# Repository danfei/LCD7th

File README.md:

LCD7th
============
It is an Arduino compatible board.
 
Schematic
------------
[PDF][schem]

BOM
------------
[CSV][bom]

PCB
------------

Photo
------------

License
------------
This project is released under the CC BY-SA license.

Support
------------
dan@szdiy.org

Where to buy
------------

[schem]:https://github.com/danfei/LCD7th/blob/master/hardware/LCD7th.pdf
[bom]:https://github.com/danfei/LCD7th/blob/master/hardware/manufature/LCD7th.csv

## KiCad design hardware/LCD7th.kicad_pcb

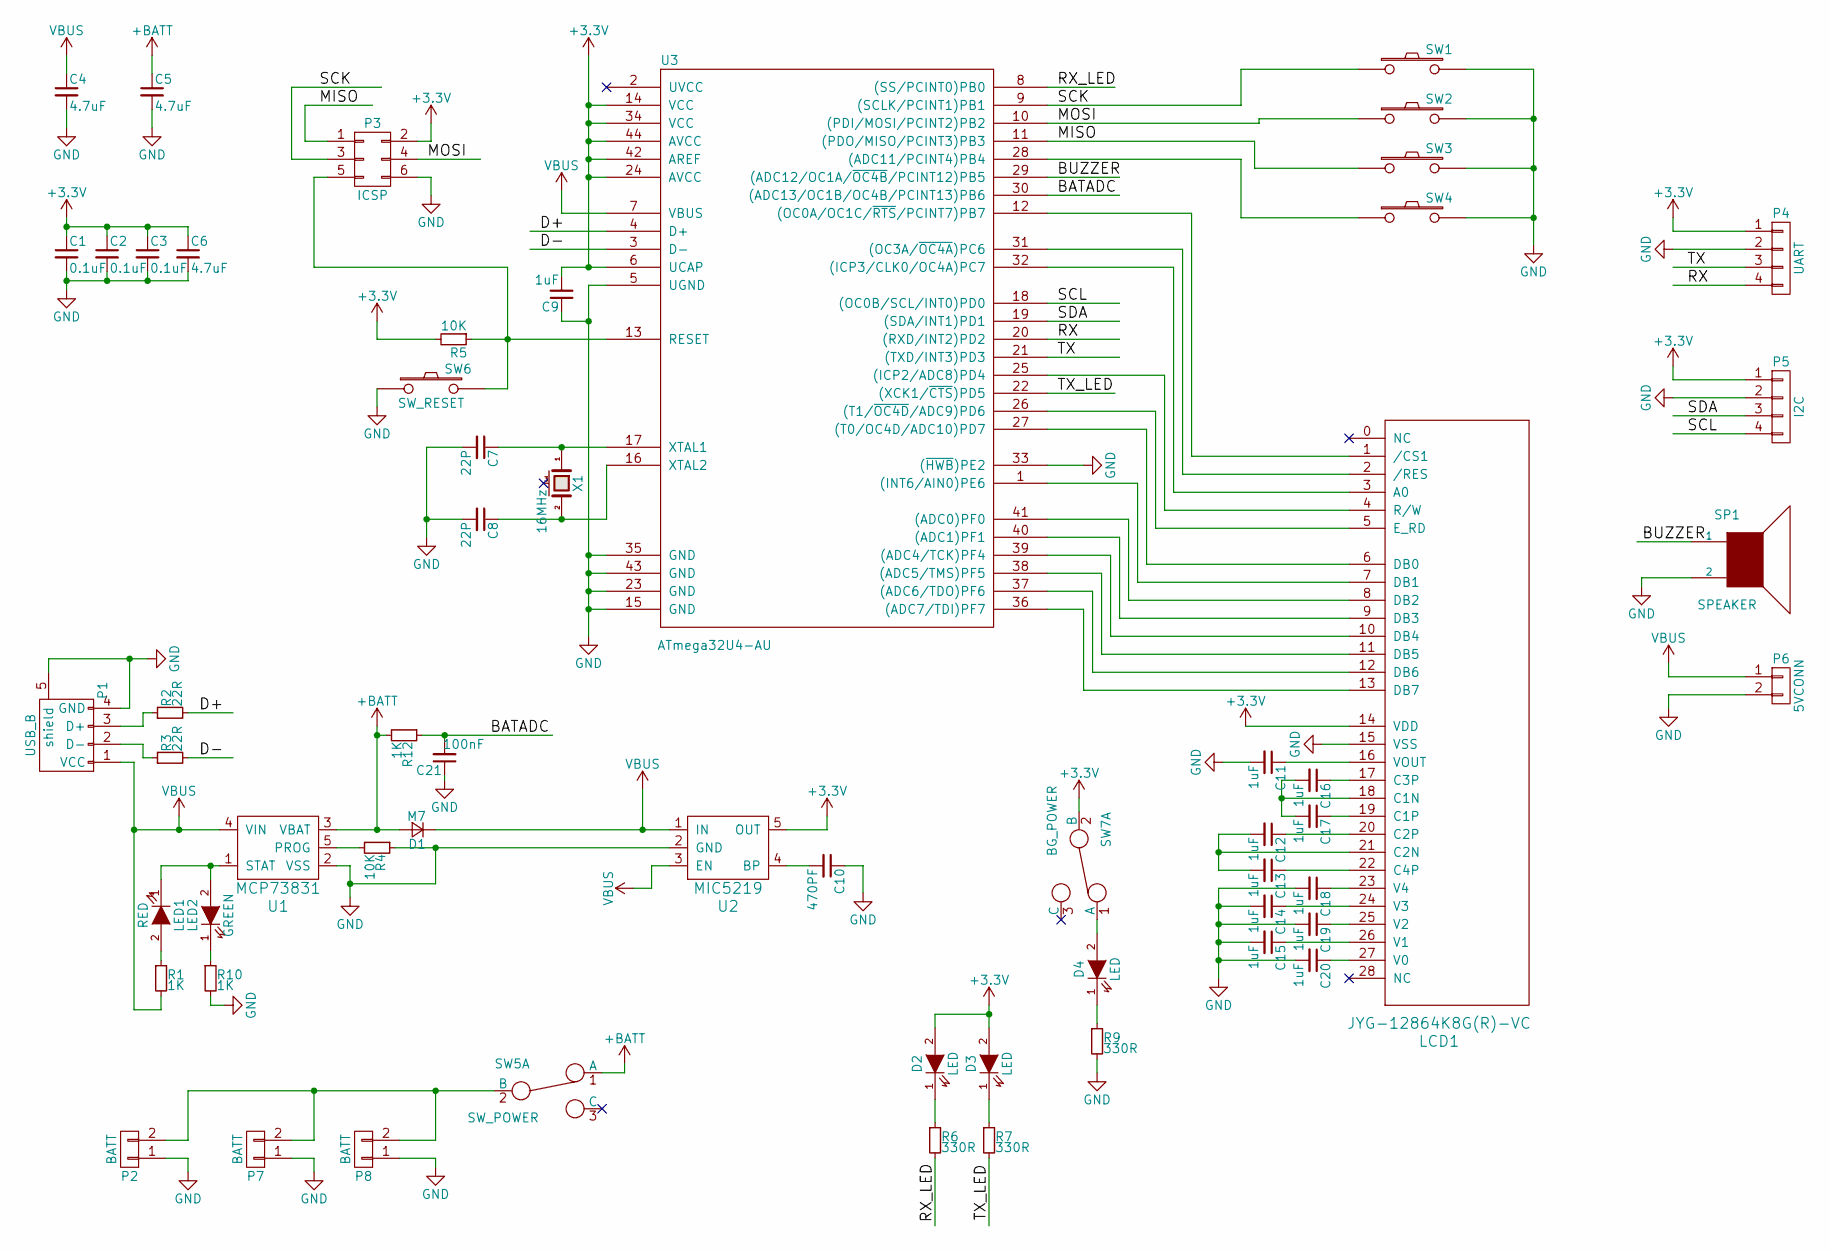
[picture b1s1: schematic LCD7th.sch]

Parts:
C1, C2, C3: 0.1uF; C_0603_HandSoldering
C4, C5, C6: 4.7uF; C_0603_HandSoldering
C7, C8: 22P; C_0603_HandSoldering
C9, C11, C12, C13, C14, C15, C16, C17, C18, C19, C20: 1uF; C_0603_HandSoldering
C10: 470PF; C_0603_HandSoldering
C21: 100nF; C_0603_HandSoldering
D1: M7; DIODE_DO214AC-SMA
D2, D3: LED; LED_0603
D4: LED; CONN_2.54mm_1x2
LCD1: JYG-12864K8G(R)-VC
LED1: RED; LED_0603
LED2: GREEN; LED_0603
P1: USB_B; USB_Micro-B
P2: BATT
P3: ICSP; Pin_Header_Straight_2x03
P4: UART; CONN_2.54mm_1x4
P5: I2C; CONN_2.54mm_1x4
P6: 5VCONN; CONN_2.54mm_1x2
P7: BATT; LiConn
P8: BATT; CR2477_s
R1, R10, R12: 1K; R_0603_HandSoldering
R2, R3: 22R; R_0603_HandSoldering
R4, R5: 10K; R_0603_HandSoldering
R6, R7, R9: 330R; R_0603_HandSoldering
SP1: SPEAKER; BUZZER
SW1: SW1; SW_SPST_EVPBF
SW2: SW2; SW_SPST_EVPBF
SW3: SW3; SW_SPST_EVPBF
SW4: SW4; SW_SPST_EVPBF
SW5: SW_POWER; SW_SPDT_PCM12
SW6: SW_RESET; SW_SPST_EVPBF
SW7: BG_POWER; SW_SPDT_PCM12
U1: MCP73831; SOT-23-5
U2: MIC5219; SOT-23-5
U3: ATmega32U4-AU; TQFP-44_10x10mm_Pitch0.8mm
X1: 16MHz; crystal_FA238-TSX3225

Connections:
+3V3: C1.1, C2.1, C3.1, C6.1, C9.2, D2.2 (A), D3.2 (A), LCD1.14 (VDD), P3.2, P4.1, P5.1, R5.2, SW7.2 (B), U2.5 (OUT), U3.6 (UCAP), U3.14 (VCC), U3.24 (AVCC), U3.34 (VCC), U3.42 (AREF), U3.44 (AVCC)
+5C: C4.1, D1.1 (K), P1.1 (VCC), P6.1, R1.2, U1.4 (VIN), U2.1 (IN), U2.3 (EN), U3.7 (VBUS)
+BATT: C5.1, D1.2 (A), R12.2, SW5.1 (A), U1.3 (VBAT)
/BATADC: C21.2, R12.1, U3.30 ((ADC13/OC1B/OC4B/PCINT13)PB6)
/BUZZER: SP1.1, U3.29 ((ADC12/OC1A/~OC4B~/PCINT12)PB5)
/D+: R2.2, U3.4 (D+)
/D-: R3.2, U3.3 (D-)
/MISO: P3.1, SW3.1, U3.11 ((PDO/MISO/PCINT3)PB3)
/MOSI: P3.4, SW2.1, U3.10 ((PDI/MOSI/PCINT2)PB2)
/RX: P4.4, U3.20 ((RXD/INT2)PD2)
/RX_LED: R6.2, U3.8 ((SS/PCINT0)PB0)
/SCK: P3.3, SW1.1, U3.9 ((SCLK/PCINT1)PB1)
/SCL: P5.4, U3.18 ((OC0B/SCL/INT0)PD0)
/SDA: P5.3, U3.19 ((SDA/INT1)PD1)
/TX: P4.3, U3.21 ((TXD/INT3)PD3)
/TX_LED: R7.2, U3.22 ((XCK1/~CTS~)PD5)
GND: C1.2, C2.2, C3.2, C4.2, C5.2, C6.2, C7.2, C8.2, C9.1, C10.1, C11.2, C14.2, C15.2, C18.2, C19.2, C20.2, C21.1, LCD1.15 (VSS), P1.4 (GND), P1.5 (shield), P2.1, P3.6, P4.2, P5.2, P6.2, P7.1, P8.1, R4.1, R9.2, R10.2, SP1.2, SW1.2, SW2.2, SW3.2, SW4.2, SW6.1, U1.2 (VSS), U2.2 (GND), U3.5 (UGND), U3.15 (GND), U3.23 (GND), U3.33 ((~HWB~)PE2), U3.35 (GND), U3.43 (GND)
unnamed: C7.1, U3.17 (XTAL1), X1.1
unnamed: C8.1, U3.16 (XTAL2), X1.2
unnamed: C10.2, U2.4 (BP)
unnamed: C11.1, LCD1.16 (VOUT)
unnamed: C12.1, LCD1.20 (C2P)
unnamed: C12.2, C13.2, LCD1.21 (C2N)
unnamed: C13.1, LCD1.22 (C4P)
unnamed: C14.1, LCD1.24 (V3)
unnamed: C15.1, LCD1.26 (V1)
unnamed: C16.1, LCD1.17 (C3P)
unnamed: C16.2, C17.2, LCD1.18 (C1N)
unnamed: C17.1, LCD1.19 (C1P)
unnamed: C18.1, LCD1.23 (V4)
unnamed: C19.1, LCD1.25 (V2)
unnamed: C20.1, LCD1.27 (V0)
unnamed: D2.1 (K), R6.1
unnamed: D3.1 (K), R7.1
unnamed: D4.1 (K), R9.1
unnamed: D4.2 (A), SW7.1 (A)
unnamed: LCD1.1 (/CS1), U3.12 ((OC0A/OC1C/~RTS~/PCINT7)PB7)
unnamed: LCD1.2 (/RES), U3.31 ((OC3A/~OC4A~)PC6)
unnamed: LCD1.3 (A0), U3.32 ((ICP3/CLK0/OC4A)PC7)
unnamed: LCD1.4 (R/W), U3.25 ((ICP2/ADC8)PD4)
unnamed: LCD1.5 (E_RD), U3.26 ((T1/~OC4D~/ADC9)PD6)
unnamed: LCD1.6 (DB0), U3.27 ((T0/OC4D/ADC10)PD7)
unnamed: LCD1.7 (DB1), U3.1 ((INT6/AIN0)PE6)
unnamed: LCD1.8 (DB2), U3.41 ((ADC0)PF0)
unnamed: LCD1.9 (DB3), U3.40 ((ADC1)PF1)
unnamed: LCD1.10 (DB4), U3.39 ((ADC4/TCK)PF4)
unnamed: LCD1.11 (DB5), U3.38 ((ADC5/TMS)PF5)
unnamed: LCD1.12 (DB6), U3.37 ((ADC6/TDO)PF6)
unnamed: LCD1.13 (DB7), U3.36 ((ADC7/TDI)PF7)
unnamed: LED1.1 (K), LED2.2 (A), U1.1 (STAT)
unnamed: LED1.2 (A), R1.1
unnamed: LED2.1 (K), R10.1
unnamed: P1.2 (D-), R3.1
unnamed: P1.3 (D+), R2.1
unnamed: P2.2, P7.2, P8.2, SW5.2 (B)
unnamed: P3.5, R5.1, SW6.2, U3.13 (RESET)
unnamed: R4.2, U1.5 (PROG)
unnamed: SW4.1, U3.28 ((ADC11/PCINT4)PB4)

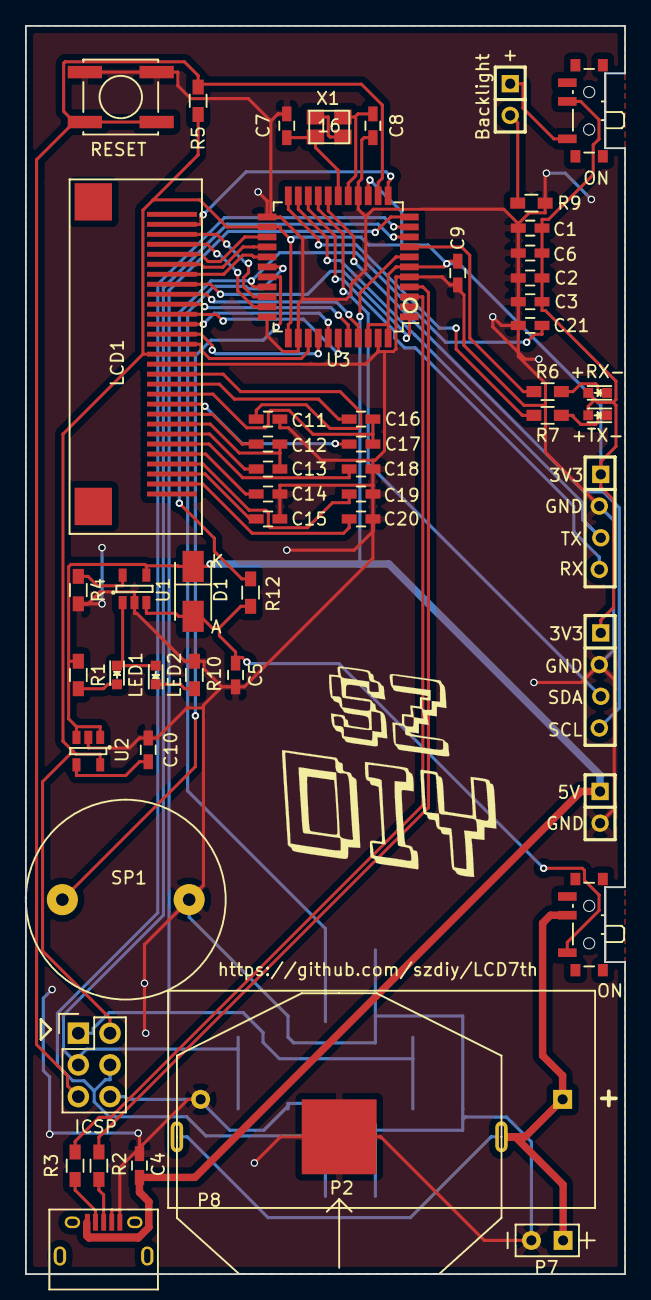
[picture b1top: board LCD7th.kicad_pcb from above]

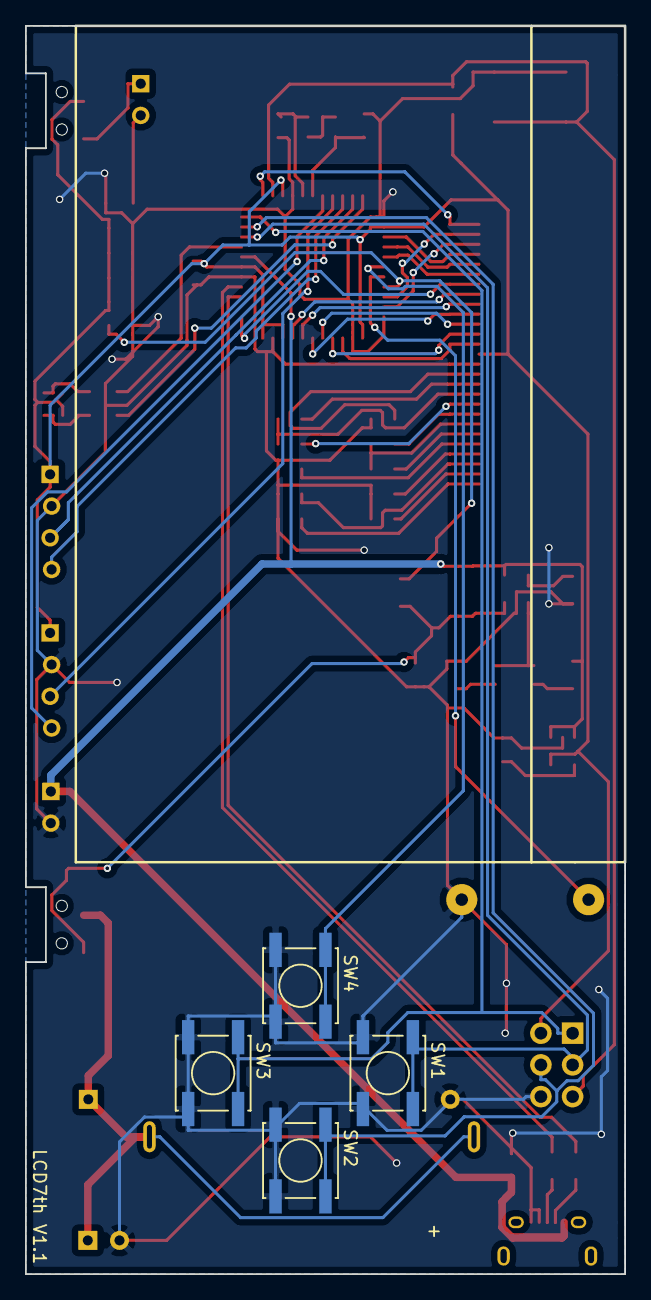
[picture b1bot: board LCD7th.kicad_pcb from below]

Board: 2 copper layers, 48.0 x 100.0 mm, 58 parts (4 on the bottom side), 58 nets.

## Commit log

2016-04-15 fix some bug
2016-04-18 add datasheet
2016-04-18 add BOM
2016-04-18 updated the readme
2016-04-18 updated the gerber
2016-04-18 updated the gerber.zip
2016-04-20 updated the demo
2017-06-25 uppdate layout
